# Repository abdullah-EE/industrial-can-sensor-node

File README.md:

# Smart Brushed DC Motor Controller and Monitor

A staged electrical and embedded-systems portfolio project for industrial, robotics, electronics, power electronics, and hardware-test internships.

## Goal

Design and later build a low-voltage brushed DC motor controller that:

- controls a small 12 V brushed DC motor with PWM
- measures motor current and supply voltage
- monitors temperature and vibration
- detects stall, overcurrent, overheating, undervoltage, sensor failure, and CAN timeout
- shuts the motor down safely during critical faults
- communicates status and commands over CAN
- starts on a dev board and moves toward a custom PCB only after the basics are proven

## Current Version 1 Direction

Version 1 uses an STM32 Nucleo board, a discrete one-direction low-side MOSFET motor switch, shunt current sensing, divided supply-voltage sensing, basic temperature sensing, an accelerometer header, and a CAN transceiver.

This is intentionally not a BLDC, FOC, cloud, AI, dashboard, or high-power motor project.

## Repository Structure

- `docs/` - research notes, requirements, architecture, design decisions, and build plan
- `hardware/bom.csv` - first-pass bill of materials
- `hardware/ltspice/` - simulation starters
- `hardware/kicad/` - KiCad hardware notes
- `kicad/` - KiCad project files
- `firmware/` - STM32 firmware scaffold

## Validation Rule

Simulation results and measured results are separate. Anything in LTspice is design exploration until it is later checked on real hardware with a current-limited supply, meter, oscilloscope, and documented test procedure.

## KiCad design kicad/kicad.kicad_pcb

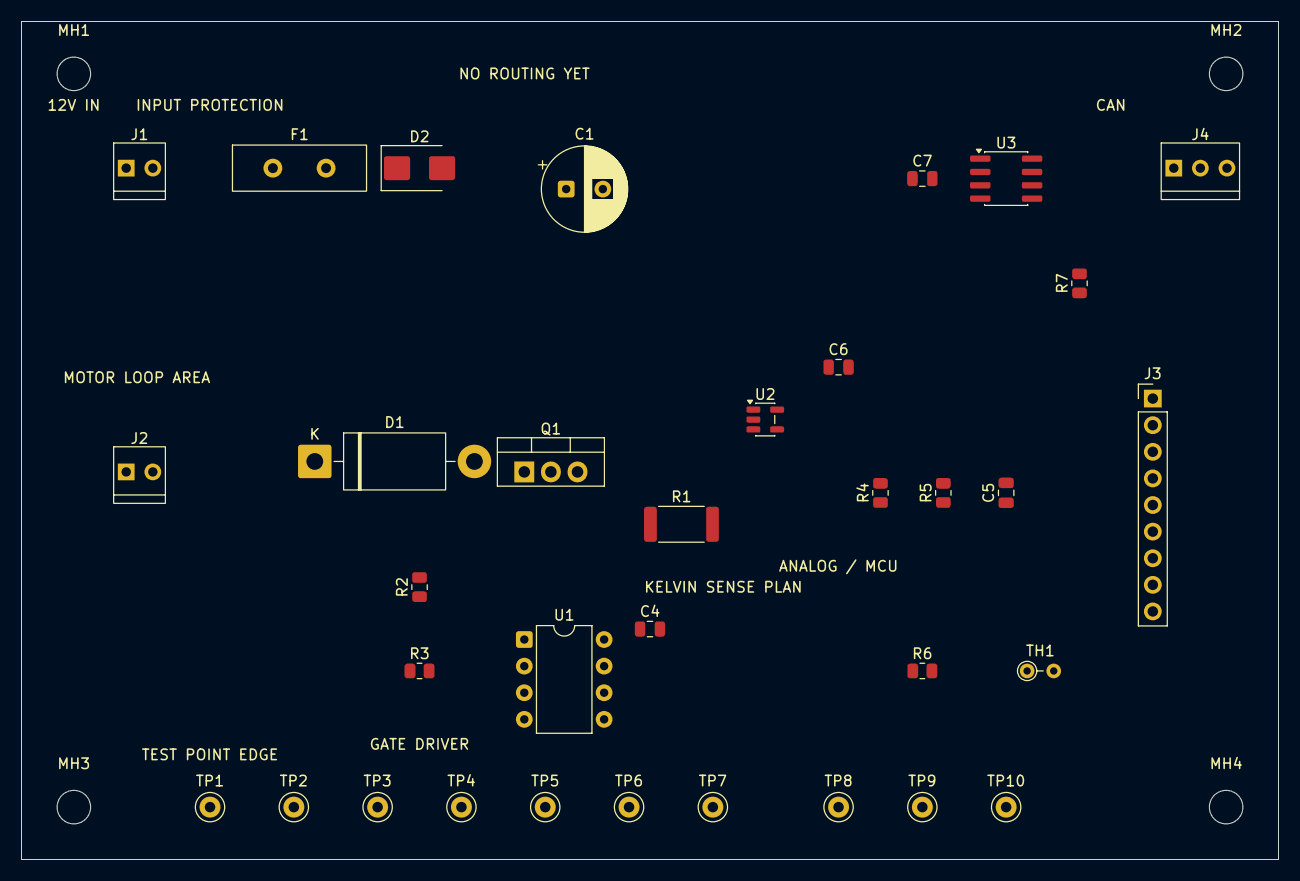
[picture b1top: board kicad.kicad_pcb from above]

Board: 2 copper layers, 120.0 x 80.0 mm, 38 parts (0 on the bottom side), 17 nets, no tracks yet.

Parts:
C1: 470uF_25V; CP_Radial_D8.0mm_P3.50mm
C4: 100nF_DRIVER; C_0805_2012Metric
C5: 47nF_VSENSE; C_0805_2012Metric
C6: 100nF_INA180; C_0805_2012Metric
C7: 100nF_TCAN332; C_0805_2012Metric
D1: 1N5822_FLYBACK; D_DO-201AD_P15.24mm_Horizontal
D2: SMBJ18A; D_SMB
F1: RXEF110_PTC; Littelfuse_RXEF110
J1: 12V_INPUT; OnShore_OSTVN02A150
J2: MOTOR_OUT; OnShore_OSTVN02A150
J3: NUCLEO_HEADER; PinHeader_1x09_P2.54mm_Vertical
J4: CAN_BUS; OnShore_OSTVN03A150
MH1, MH2, MH3, MH4: M3; MountingHole_3.2mm_M3
Q1: IRLZ44NPBF; TO-220-3_Vertical
R1: 0.05R_SHUNT; R_2512_6332Metric
R2: 22R_GATE; R_0805_2012Metric
R3: 100k_GATE_PD; R_0805_2012Metric
R4: 100k_VSENSE_TOP; R_0805_2012Metric
R5: 27k_VSENSE_BOTTOM; R_0805_2012Metric
R6: 10k_TEMP_TOP; R_0805_2012Metric
R7: 120R_CAN_TERM; R_0805_2012Metric
TH1: 10k_NTC; R_Axial_DIN0204_L3.6mm_D1.6mm_P2.54mm_Vertical
TP1: VMOTOR_12V; TestPoint_Keystone_5000-5004_Miniature
TP2: MOTOR_SW; TestPoint_Keystone_5000-5004_Miniature
TP3: PWM_GATE; TestPoint_Keystone_5000-5004_Miniature
TP4: MOTOR_CURRENT_SHUNT_HI; TestPoint_Keystone_5000-5004_Miniature
TP5: ISENSE_ADC; TestPoint_Keystone_5000-5004_Miniature
TP6: VSENSE_ADC; TestPoint_Keystone_5000-5004_Miniature
TP7: TEMP_ADC; TestPoint_Keystone_5000-5004_Miniature
TP8: CANH; TestPoint_Keystone_5000-5004_Miniature
TP9: CANL; TestPoint_Keystone_5000-5004_Miniature
TP10: PGND; TestPoint_Keystone_5000-5004_Miniature
U1: TC4427ACPA; DIP-8_W7.62mm
U2: INA180A1IDBVR; SOT-23-5
U3: TCAN332DR; SOIC-8_3.9x4.9mm_P1.27mm

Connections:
/CANH: J4.1, R7.1, TP8.1, U3.7
/CANL: J4.3, R7.2, TP9.1, U3.6
/CAN_RX: J3.6, U3.4
/CAN_TX: J3.5, U3.1
/GATE_DRV_OUT: R2.1, U1.7
/ISENSE_ADC: J3.2, TP5.1, U2.1
/MOTOR_CURRENT_SHUNT_HI: Q1.3, R1.1, TP4.1, U2.4
/MOTOR_SW: D1.2, J2.2, Q1.2, TP2.1
/PGND: C1.2, C4.2, C5.2, C6.2, C7.2, D2.2, J1.2, J3.9, J4.2, R1.2, R3.2, R5.2, TH1.2, TP10.1, U1.3, U1.4, U2.2, U2.3, U3.2
/PWM_FROM_STM32: J3.1, U1.2
/PWM_GATE: Q1.1, R2.2, R3.1, TP3.1
/TEMP_ADC: J3.4, R6.2, TH1.1, TP7.1
/VDD_3V3: C6.1, C7.1, J3.7, R6.1, U2.5, U3.3
/VDD_5V: C4.1, J3.8, U1.6
/VIN_12V: F1.2, J1.1
/VMOTOR_12V: C1.1, D1.1, D2.1, F1.1, J2.1, R4.1, TP1.1
/VSENSE_ADC: C5.1, J3.3, R4.2, R5.1, TP6.1
